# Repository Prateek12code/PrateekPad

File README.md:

# PrateekPad – 9-Key OLED Macropad

PrateekPad is my custom 9-key macropad built completely from scratch.  
This was my first time designing a PCB, writing firmware for a microcontroller, and building a full 3D printed enclosure around it.

I started this project with zero experience in hardware design. Now it’s a fully working macropad with an OLED display, rotary encoder, custom PCB, and layered firmware system.

---

## Overview

PrateekPad is a compact productivity macropad powered by the **Seeed XIAO RP2040**.

Features include:

- 9 mechanical keys arranged in a **3×3 matrix**
- **Rotary encoder** with press functionality
- **128×32 I2C OLED display**
- **KMK firmware**
- **Layer switching system**
- **Custom 2-layer PCB**
- **Fully 3D-printed enclosure**

The goal of this project was to learn the complete workflow of designing a hardware product from scratch.

---

## Assembled Model & Case Model

This shows the full assembled design including the case, switches, OLED display, and rotary encoder.

---

## PCB Layout

A custom **2-layer PCB** was designed for the macropad using KiCad.  
It integrates the switch matrix, OLED connections, rotary encoder, and the Seeed XIAO RP2040.

---

## Schematic

The schematic shows the switch matrix, diode configuration, rotary encoder wiring, and OLED interface.

---

## Firmware

The firmware is written using **KMK**, which runs on the RP2040 microcontroller.

The macropad supports multiple layers that allow it to be used for:

- Coding shortcuts
- Media control
- Editing shortcuts
- Numpad input

The OLED display provides quick visual feedback about the current layer.

---

## Design Constraints

This project follows the Hackpad design rules:

- Through-hole **Seeed XIAO RP2040**
- **2-layer PCB**
- PCB under **100mm × 100mm**
- Case under **200mm × 200mm × 100mm**
- Fewer than **16 inputs**
- **Fully 3D printed enclosure**

---

## What I Learned

This project helped me learn many hardware design concepts including:

- Designing and routing a PCB
- Matrix scanning for keyboards
- Firmware development with KMK
- Mechanical design for 3D printing
- Creating production-ready manufacturing files

---

Built by **Prateek**.

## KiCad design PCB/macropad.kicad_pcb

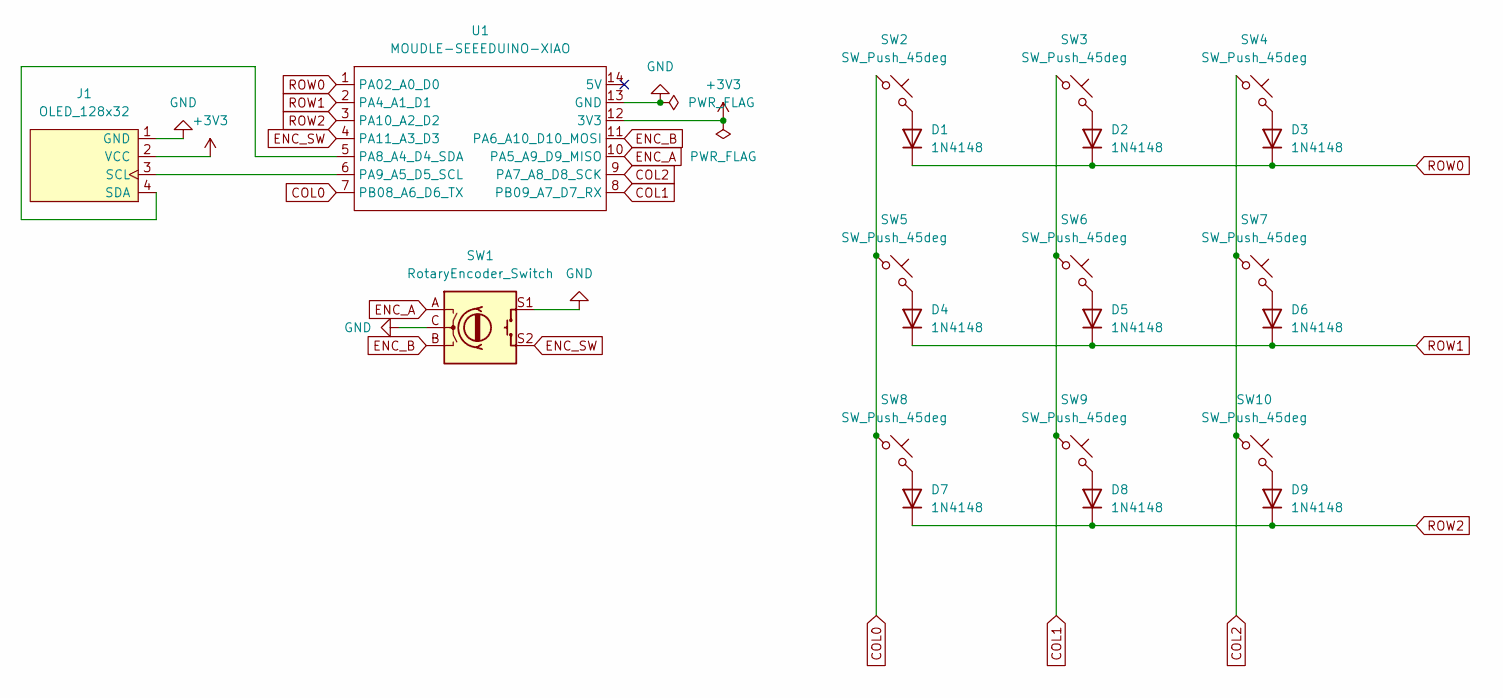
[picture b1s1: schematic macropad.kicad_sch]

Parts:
D1, D2, D3, D4, D5, D6, D7, D8, D9: 1N4148; D_DO-35_SOD27_P7.62mm_Horizontal
J1: OLED_128x32
SW1: RotaryEncoder_Switch; RotaryEncoder_Alps_EC11E-Switch_Vertical_H20mm
SW2, SW3, SW4, SW5, SW6, SW7, SW8, SW9, SW10: SW_Push_45deg; MX_PCB_1.00u
U1: MOUDLE-SEEEDUINO-XIAO; Seeed_XIAO_RP2040

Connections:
+3V3: J1.2 (VCC), U1.12 (3V3)
COL0: SW2.1, SW5.1, SW8.1, U1.7 (PB08_A6_D6_TX)
COL1: SW3.1, SW6.1, SW9.1, U1.8 (PB09_A7_D7_RX)
COL2: SW4.1, SW7.1, SW10.1, U1.9 (PA7_A8_D8_SCK)
ENC_A: SW1.A, U1.10 (PA5_A9_D9_MISO)
ENC_B: SW1.B, U1.11 (PA6_A10_D10_MOSI)
ENC_SW: SW1.S2, U1.4 (PA11_A3_D3)
GND: J1.1 (GND), SW1.C, SW1.S1, U1.13 (GND)
unnamed: D1.2 (A), SW2.2
unnamed: D2.2 (A), SW3.2
unnamed: D3.2 (A), SW4.2
unnamed: D4.2 (A), SW5.2
unnamed: D5.2 (A), SW6.2
unnamed: D6.2 (A), SW7.2
unnamed: D7.2 (A), SW8.2
unnamed: D8.2 (A), SW9.2
unnamed: D9.2 (A), SW10.2
unnamed: J1.3 (SCL), U1.6 (PA9_A5_D5_SCL)
unnamed: J1.4 (SDA), U1.5 (PA8_A4_D4_SDA)
ROW0: D1.1 (K), D2.1 (K), D3.1 (K), U1.1 (PA02_A0_D0)
ROW1: D4.1 (K), D5.1 (K), D6.1 (K), U1.2 (PA4_A1_D1)
ROW2: D7.1 (K), D8.1 (K), D9.1 (K), U1.3 (PA10_A2_D2)

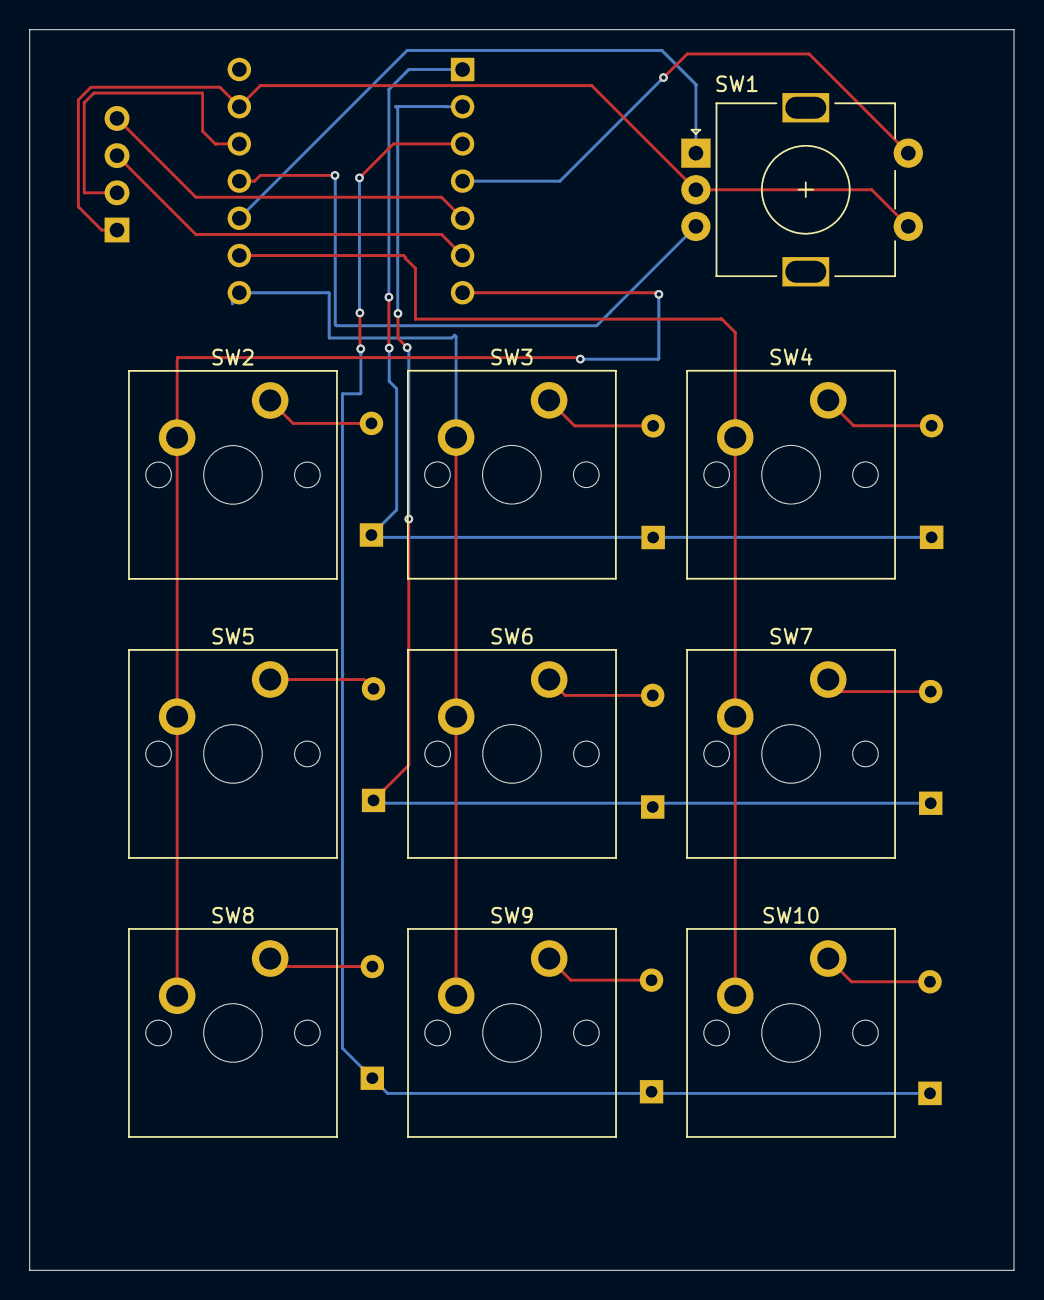
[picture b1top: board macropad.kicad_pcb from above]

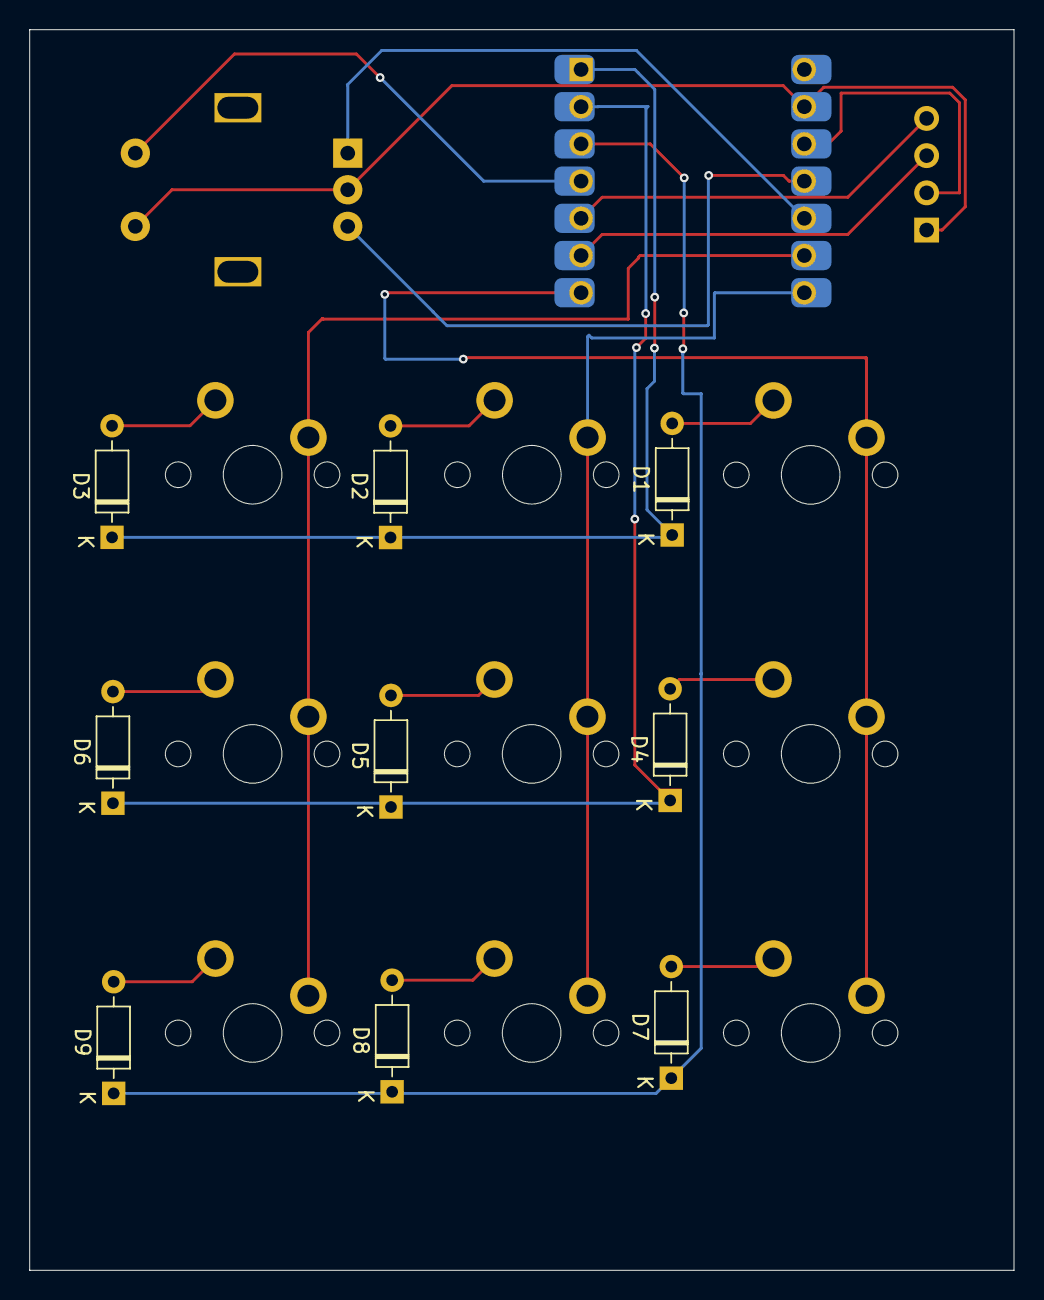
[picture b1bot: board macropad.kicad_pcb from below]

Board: 2 copper layers, 67.2 x 84.7 mm, 21 parts (10 on the bottom side), 22 nets.

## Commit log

2026-03-02 Add greeting message to README
2026-03-02 Create hi
2026-03-02 Rename Screenshot 2026-03-02 233448.png to pcb.png
2026-03-02 Rename Screenshot 2026-03-02 233532.png to case.png
2026-03-02 Rename macropad.png to schematic
2026-03-02 Rename schematic to schematic.png
2026-03-02 Update README with PrateekPad project details
    Added detailed project description for PrateekPad, including features, design process, and lessons learned.
2026-03-02 Remove case image from README
    Removed image of the case from the README.
2026-03-02 Fix image extension for schematic in README
2026-03-02 Rename section 'Full Assembly' to 'Case'
2026-03-04 Rename Screenshot 2026-03-04 232946.png to assembled.png
2026-03-04 Revise README for PrateekPad project details
    Updated README.md for clarity and formatting improvements.
2026-03-04 Rename Screenshot 2026-03-05 040053.png to assembled.png
2026-03-04 Revise README for assembled model and case design
    Updated section titles and removed case design details.
